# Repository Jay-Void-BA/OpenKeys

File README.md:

# OpenKeys — Classical edition

开源 USB / NFC 认证器，面向个人制作的 **3 把密钥**。当前电路为 **R0.5：本地六位 PIN、十个数字实体键、DFR0555 双行 LCD**；自研运行代码采用 Rust。

> **工程候选，生产放行 BLOCKED。** 已有已布线电路板、制造文件、板级诊断和经过测试的安全模块。完整生产 Root、认证协议与管理通道的实机集成尚未完成，不能将当前诊断固件用于真实账户。

[当前进度](docs/DEVELOPMENT_STATUS.md) · [文档导航](docs/README.md) · [硬件与图纸](hardware/r05/README.md) · [从原材料开始制作](manufacturing/BUILD_R05_ZH.md) · [安全复查](docs/SECURITY_REVIEW_R05.md)

**当前 `main` 为优先开发的经典版，不含 SM2 或后量子算法。** ML-DSA-65 / ML-KEM-768 留在独立的 [PQC 分支](https://github.com/Jay-Void-BA/OpenKeys/tree/pqc)，暂缓实现。两版都优先选择外国芯片，中国芯片作为备选，并核实大陆交付 / 个人三件采购；见[分版规则](docs/EDITIONS.md)。已将安全芯片候选调整为支持传统 RSA 的 SE051C2；见[选型与供电修订](docs/CLASSICAL_SE_POWER_R05.md)。实片 profile / PIN 权限及 RSA 固件仍待集成验证。

*工程图，非实物照片。板体 96 × 112 mm；外壳候选 102 × 118 × 30 mm，待试装。*

## 当前固定需求

| 项目 | 设计目标与现状 |
|---|---|
| 本地身份验证 | 首次开机在钥匙设置六位数字 PIN，十个独立 GPIO 键；没有指纹。改硬件 PIN 清空全部用户数据，第 11 次完整错误猜测触发清空；完整销毁服务尚待集成 |
| 会话授权 | 硬件 PIN 与各协议 PIN 分别缓存，同一已配对认证会话中 30 秒无有效操作锁定；连接 / 保活不续期，断连 / NFC 离场立即锁定，敏感操作仍需实体确认 |
| 显示 | 英文 16 × 2 LCD，DFRobot DFR0555 蓝底白字；现货及版本说明见硬件页 |
| 认证 | FIDO2 / WebAuthn / Passkey、U2F、hmac-secret、凭据管理；OpenPGP / PIV / SSH 为新增待集成目标 |
| OTP 与记录 | TOTP / HOTP 种子不可导出，六位码仅钥匙 LCD 显示；加密 notes / recovery codes；均受本地 PIN 约束 |
| 接口 / 电源 | 唯一外部 USB-C 母口，USB 2.0 数据兼 5 V 充电，另有 NFC；保护型 500 mAh 电池与真实 NTC |
| 管理器 | GPUI 英文桌面原型；macOS / Windows / Linux USB，iOS NFC / USB-C、iPadOS USB-C、Android NFC / USB-C 为交付目标，真实设备后端和移动安装包尚未完成 |

Apple 20 W 充电器使用 **5 V**，不申请 9 V PD。设计输入预算 **0.50 W**，电池侧充电目标上限约 **0.42 W**，实际受负载、温度和限流影响；诊断镜像关闭充电。

## 从这里开始

| 目的 | 入口 |
|---|---|
| 查看电路、PCB、BOM、结构和制造包 | [R0.5 硬件](hardware/r05/README.md) |
| 了解哪些完成、哪些不能交付 | [状态](docs/DEVELOPMENT_STATUS.md)、[安全复查](docs/SECURITY_REVIEW_R05.md) |
| 构建与检查 | [开发起步](docs/GETTING_STARTED.md)、[R05 目标](firmware/r05/README.md)、[GPUI 管理器](apps/manager-gpui/README.md)、[开发包](docs/NATIVE_BUILDS_R05.md) |
| 核查 PIN 缓存与 NFC 边界 | [会话规则](docs/PIN_SESSIONS_R05.md)、[架构](docs/ARCHITECTURE.md) |
| 从原材料、订板到代焊和测试 | [制作手册](manufacturing/BUILD_R05_ZH.md)、[境内渠道](manufacturing/MAINLAND_COMPONENT_CHANNELS.md) |
| 委托个人 / 小批量工厂、实验室 | [机构筛选](manufacturing/MAINLAND_SUPPLIERS_AND_LABS.md)、[资格确认](manufacturing/REQUEST_FOR_CONFIRMATION.md) |
| 比较已拉取的开源实现 | [PicoKeys / OpenSK / CanoKey / SoloKeys 参考](docs/UPSTREAM_REVIEW_R05.md) |

## 检查的含义

R05 当前有 14 页原理图、209 个 BOM 位置、四层已布线 PCB；ERC / DRC 零错误、零警告、零未连接，1187 项独立板网核对通过。[CAD 清单](hardware/r05/review/cad-manifest.json)绑定导出文件。独立备份、主动防拆和隔离采样的[专项测试](manufacturing/BACKUP_TAMPER_TESTS_R05_ZH.md)另行验收；新增五路 NFC 隔离与 VCC 反向阻断须按[NFC 专项规程](manufacturing/NFC_ISOLATION_TESTS_R05_ZH.md)验证。设计文件的规则和连通性不能证明实物抗侧信道、故障注入、EMC、RF、充电或抗拆安全。

新代码的[本地检查记录](docs/r05-validation.json)与 CI 以对应提交为准；[R04 的历史 CI](docs/ci-evidence-r04.json)不能作为 R05 的通过证明。[生产缺口](docs/DEVELOPMENT_STATUS.md)逐项列出，完整 Root 和硬件 PIN 的 SE 原生强制仍是关键未关闭项。

```text
hardware/r05/      当前电路、PCB、BOM、机械和制造导出
firmware/r05/      与 R05 已保存板绑定的 ARM 电气诊断
firmware/board/    LCD、十键、PIN 输入、OTP 等候选驱动
crates/           授权、协议适配、SE、加密通信和存储模块
apps/manager-gpui/ GPUI 管理器原型；设备后端尚未接通
manufacturing/    制作、渠道、委托和验收资料
docs/             状态、安全边界、会话和参考复核
vendor/           固定第三方来源、许可和可核查补丁
```

自研源码采用 [MIT](LICENSE)，硬件采用 [CERN-OHL-S-2.0](hardware/LICENSE-CERN-OHL-S-2.0.txt)；第三方代码保留各自许可。历史 R04 指纹 / 四键资料从[硬件导航](hardware/README.md)进入，不能与 R05 混用。

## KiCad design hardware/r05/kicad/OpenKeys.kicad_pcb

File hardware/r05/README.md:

# OpenKeys R0.5：PIN＋十键

[项目首页](../../README.md) · [状态](../../docs/DEVELOPMENT_STATUS.md) · [安全复查](../../docs/SECURITY_REVIEW_R05.md) · [制作与测试](../../manufacturing/BUILD_R05_ZH.md)

本版正式取消指纹。身份验证使用设备本地 **6 位数字 PIN**，0–9 十个独立实体键；电脑和手机均不输入设备 PIN。保留 FIDO2 / U2F / hmac-secret、可信请求确认、凭据管理和加密 notes / recovery codes 的目标范围。新增 TOTP / HOTP、OpenPGP / PIV / SSH 目标；动态验证码仅钥匙 LCD 显示，种子不可导出。

**工程样板候选，生产放行仍为 BLOCKED。** CAD 检查、Rust 模型测试与诊断固件不能替代生产 Root、实片配置和物理安全验收。不得给三把最终密钥写入真实账户或恢复码。

## 文件

| 内容 | 入口 |
|---|---|
| 整机尺寸与真实 PCB 线条 | [装配图 PDF](exports/OpenKeys-dimensions.pdf)、[PNG](exports/OpenKeys-dimensions.png)、[坐标 JSON](mechanical/dimensions.json) |
| 电路 | [14 页原理图 PDF](exports/OpenKeys-schematic.pdf)、[KiCad 源](kicad/OpenKeys.kicad_sch)、[网表](exports/OpenKeys-netlist.xml) |
| PCB | [四层板源](kicad/OpenKeys.kicad_pcb)、[正面](exports/OpenKeys-PCB-front.svg)、[背面](exports/OpenKeys-PCB-back.svg) |
| 工程打样资料 | [Gerber / 钻孔](exports/OpenKeys-fabrication.zip)、[BOM](BOM.csv)、[贴片坐标](exports/OpenKeys-SMD-position.csv)、[引脚表](pinout.csv) |
| 结构 | [OpenSCAD](mechanical/enclosure.scad)、[板体 STEP](exports/OpenKeys-PCB.step)、[结构导出](exports) |
| 检查 | [ERC](review/erc.json)、[DRC](review/routed-drc.json)、[独立网表核对](review/netlist-check.json)、[板网核对](review/board-check.json)、[摘要](review/cad-manifest.json) |
| 模拟范围 | [天线 / 复位 RC](review/simulation.json)、[输入保护直流角落](review/protection-calculations.json)、[LCD 电压静态角落](review/lcd-voltage-window.json)、[LCD 断电假设模型](review/display-power-model.json)、[备份 / 主动防拆 / ADC 模型](review/backup-tamper-model.json) |

硬件 PIN 与协议 PIN 分别按[同一认证会话的 30 秒规则](../../docs/PIN_SESSIONS_R05.md)缓存；断连 / NFC 离场立即锁定。改硬件 PIN 或第 11 次完整错误须清空全部数据；当前仅擦除锁存，完整销毁服务待集成。

## 经典版 SE 与辅助电源

U5 为 SE051C2HQ1/Z01XDZ / OEF A8FA / Applet 7.2 候选，保留 H573 单 SE 架构，纠正原 E2 不支持 RSA 的限制。VBAT 改用独立预焊脚 CR-2032/HFN，经 10k 限流和 LM66100 反向阻断；CE 必须接 VOUT，不能接地。C41 / C56 在 MCU VBAT 就近去耦。PA1 的硬件 TAMP_OUT4 经三个分散的内部壳体触点返回 PC13 / TAMP_IN1；另一触点 SW12 独立复位。U27 / U24 / U25 / U26 对主动回路失配进行整形、比较、滤波和硬件复位，没有软件使能旁路。备份 SRAM 关闭，连续性锚点使用备份寄存器；Root 连续性集成与实片验证仍是交付条件。

电量采样的 330k / 330k 分压器与储能电容在 TMUX1511 的隔离侧，ADC 侧有 100k 下拉；硬复位切断采样通路。计入下拉负载，正常采样比例为 **100/530**，仍不能把电量电压当成已校准百分比。[电源依据与采购](../../docs/CLASSICAL_SE_POWER_R05.md)、[备份防拆与采样测试](../../manufacturing/BACKUP_TAMPER_TESTS_R05_ZH.md)。

NFC 另增加五路 TMUX1511 信号隔离和 LM66100 VCC 反向阻断，主轨 R69 改 9.1k 泄放；总数 **209 个 BOM 位置**。全部信号隔离的使能硬接 NRST，RF 侧与主机侧不共用铜线。20µA 反灌分配和 <=2MHz 初始 SPI 限制尚待实测，不能外推 ±2µA 的零供电指标到任意电源爬升或强场；见[电路依据](../../docs/CLASSICAL_NFC_ISOLATION_R05.md)、[实板规程](../../manufacturing/NFC_ISOLATION_TESTS_R05_ZH.md)。原生 PIN / RSA、生产 Root 和全数据销毁仍需实际集成；LCD 修订见[电路依据与实测条件](../../docs/CLASSICAL_LCD_POWER_R05.md)。

## LCD 采购与兼容性

选用 **DFRobot DFR0555**：16×2 字符 LCD、蓝底白字、可调背光、I2C、标称 3.3–5V、模块外形 87×32×13mm。2026-11-10 中国大陆[官方商城](https://www.dfrobot.com.cn/goods-1697.html)页面标价 **¥55，显示“有货”**。这是页面核验，未预订三件，也不能保证下单时的库存或发货时间。先确认版本、境内发货和同批数量，再买一个尺寸样品。

[官方文档](https://wiki.dfrobot.com/dfr0555/docs/24390)区分 V1.0 与 V1.1：字符地址均为七位 `0x3E`，背光分别为 `0x60`、`0x6B`。BOM 固定 V1.1；若收到 V1.0，必须改用明确标注的 V1.0 诊断镜像并重新冻结配置，禁止自动探测降级。Rust 驱动见 [dfr0555.rs](../../firmware/board/src/dfr0555.rs)，参考寄存器来源见[来源记录](../../docs/DFR0555_SOURCE.md)。

模块无外部复位脚，因此使用锁存切电和 TCA9517A 双线隔离。U17 TPS3808 的 CT 通过 100k 接 VDD，复位释放后保持清除 180–420ms；必须在其后有新的 PC4 上升沿才能恢复供电。330Ω / 0.25W / 1206 泄放、未上电 ON 下拉和 500ms 软件关断保持用于限制残留。模型依赖“总电容≤100µF、关断注入≤20µA、关断延迟≤5ms”等**待测条件**。背光熄灭本身不等于文字消失。

LCD 改从 **SYS 经负载开关**供电，主电源强制 PWM；独立 U22 监测 SYS 窗口。计入参考 / 电阻 / 输入偏置误差，且假设开关加线束压降≤50mV，静态 LCD 范围为约 **3.3746–4.8596V**。U21 两侧分别为主 3.3V 和 LCD 电源，U23 将 EN 转为对应电平。实测纹波、背供电、功耗、低电量和故障瞬态仍是交付条件；不能把 LCD 高侧接到 MCU / SE 总线。

## 布局与按键

主板本体 96×112×1.0mm，USB 小舌部伸出 2.5mm，总包络 96×114.5mm。外壳候选 102×118×30mm。较大的现货 LCD 需要更大外壳，R0.4 的外壳不兼容。

| 场景 | 实体按键功能 |
|---|---|
| 请求到达，尚未授权 | 5 开始本地 PIN；0 取消。仅接收主机请求不扣 PIN 次数 |
| 输入 PIN | 短按 0–9 输入；长按 9 删除一位；长按 0 取消；只显示星号，满 6 位提交 |
| 验证后审阅请求 | 2 上一页，8 下一页，5 确认，0 取消；完整身份各页写入成功后才能确认 |
| 换场景 / 故障 | 丢弃按住的键，要求全部释放；复位、时钟回退、超时、断连撤销授权 |

采用专用 GPIO，没有键盘矩阵和二极管鬼键问题。25ms 去抖，800ms 长按，只在稳定释放时产生一次事件；组合键、滚键、过长按住和轮询间断不产生确认。[实际 MCU 引脚](pinout.csv)与[目标固件构建约束](../../firmware/r05/build.rs)共同核对，禁止向 R0.4 板烧录 R0.5 镜像。

## 电源、NFC 与制造边界

只有一个外部 USB-C 母口，USB 2.0 数据兼 5V 充电；没有 USB-A。可用合规 USB-C 线接 Apple 20W 充电器，不申请 PD 的 9V 档。设计输入 100mA、约 **0.50W**；电池充电目标 100mA、最高约 **0.42W**，还会受系统负载和输入限流影响。当前诊断镜像保持充电禁止，并非可充电成品固件。

保护型 1S 500mAh 电池须有真实贴附的 10k NTC，先测连接器极性。NFC 沿板左侧布置，不在绕组背后放电池、金属或地平面；LCD 和 PIN 操作需要电池供电且主开关开启，未设计成纯 NFC 取电。旋转后的线圈仍须在实际外壳、电池、手持状态下重新调谐和做手机测试。

J7 是内部 LCD 线束，J2/J6 为内部电池 / NTC；J3 为生产 DNP 的内部调试位置，均不应暴露为第二外部接口。原理图的监督器、SE 使能门和壳体触点提供故障处理路径，不能保证任意短脉冲、桥接、激光或探针攻击均被阻断。

## 重建与核对

使用 KiCad 9、Python 3 / pcbnew，附加导出使用 CairoSVG、OpenSCAD、ngspice 47。日常检查运行 `tools/export.sh`，核对**保存的已布线板**；不要默认重建 / 自动布线。`board.py` 无参数会覆盖布局，只有修改硬件并另行评审时使用。自动路由器不是 CI 的组成部分。

电路或模型修改后，先用 `python3 tools/simulate.py` 与 `python3 tools/calculate_backup.py` 明确重跑被动模拟，再导出。后者保存器件 / 语义网表 / 模型源码摘要；`--check` 和 CAD CI 只核对这些绑定，不声称重新执行 SPICE。所有模型中假定的耗流、容量、漏电、延迟和阈值须按实测更新。

许可：[CERN-OHL-S-2.0](../LICENSE-CERN-OHL-S-2.0.txt)。模型和图纸均标为工程候选；尺寸试装、DFM、EMC / ESD、故障注入和侧信道的实物结果仍为 NOT_RUN。

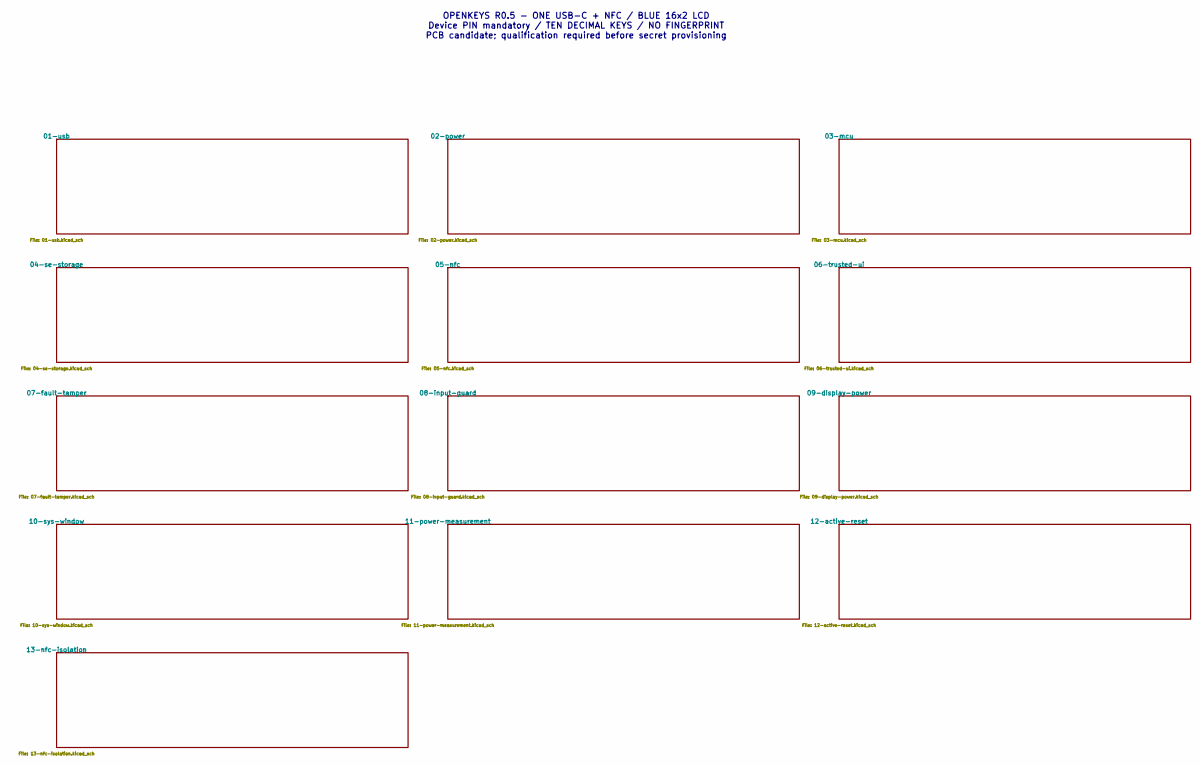
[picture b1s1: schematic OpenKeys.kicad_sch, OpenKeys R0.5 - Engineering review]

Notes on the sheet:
OPENKEYS R0.5 - ONE USB-C + NFC / BLUE 16x2 LCD Device PIN mandatory / TEN DECIMAL KEYS / NO FINGERPRINT PCB candidate; qualification required before secret provisioning

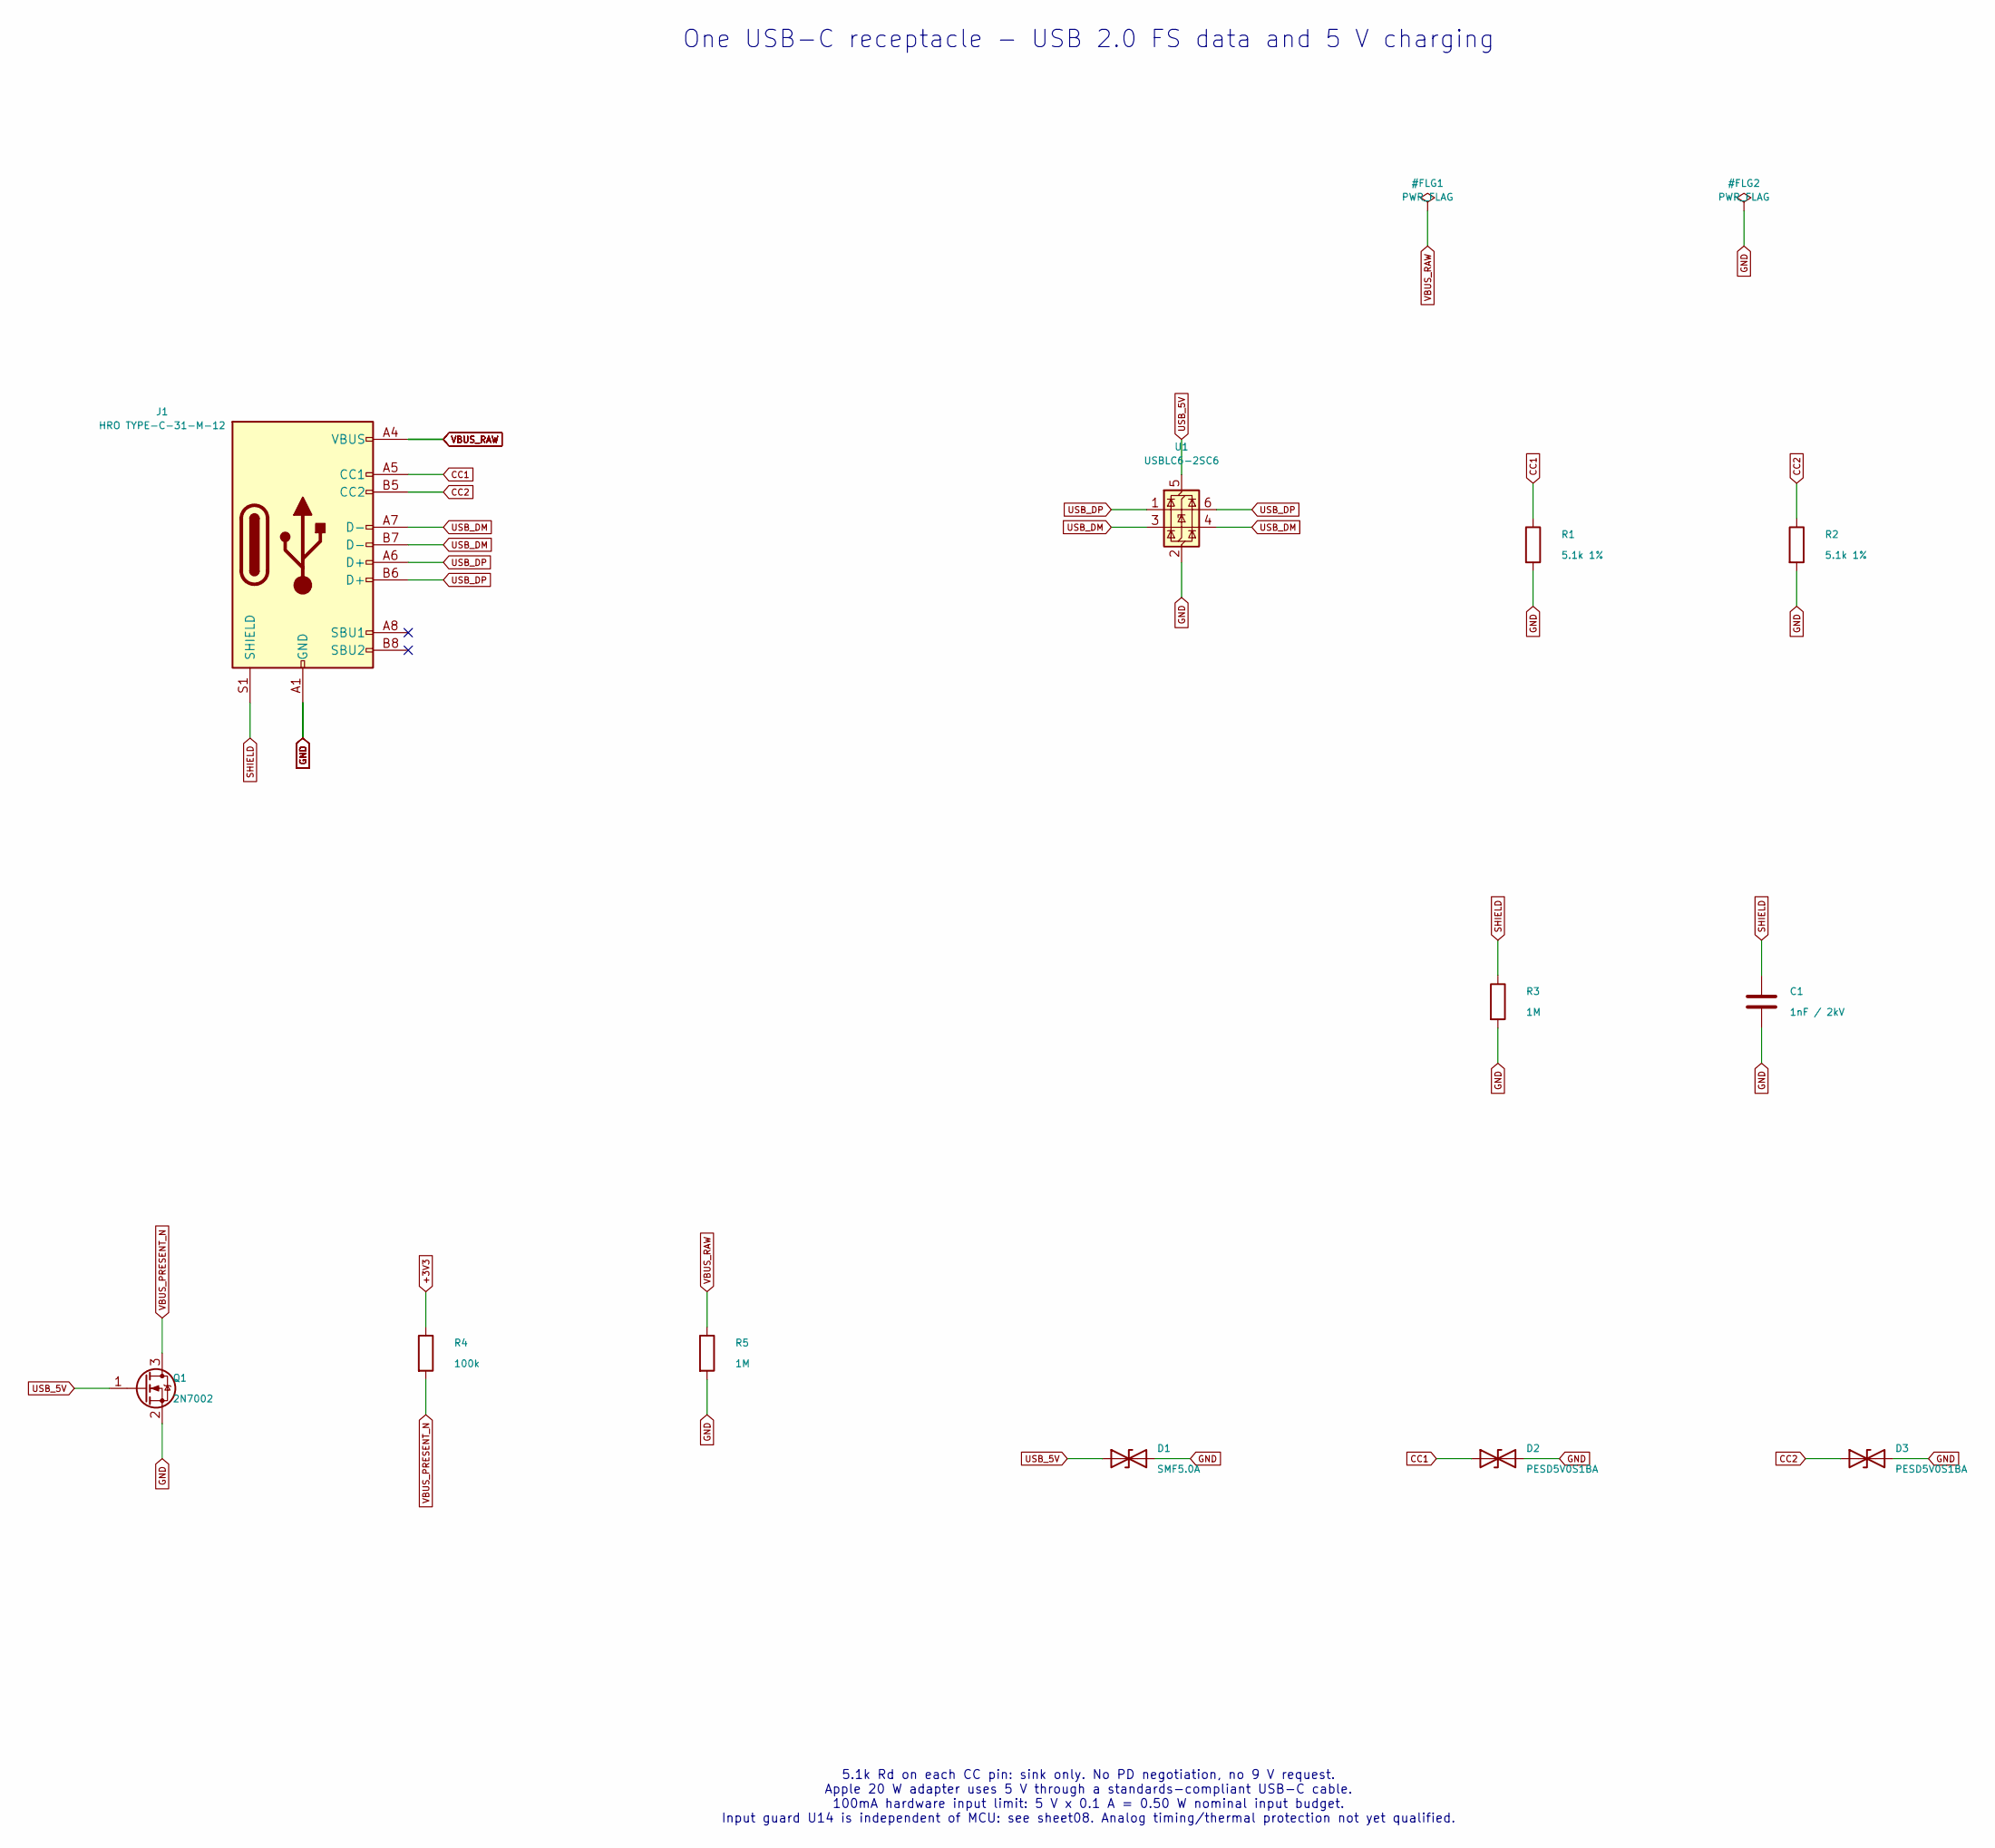
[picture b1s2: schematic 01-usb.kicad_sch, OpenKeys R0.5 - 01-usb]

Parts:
C1: 1nF / 2kV; C_1206_3216Metric
D1: SMF5.0A; D_SOD-123F
D2, D3: PESD5V0S1BA; D_SOD-323
J1: HRO TYPE-C-31-M-12; USB_C_Receptacle_HRO_TYPE-C-31-M-12
Q1: 2N7002; SOT-23
R1, R2: 5.1k 1%; R_0603_1608Metric
R3, R5: 1M; R_0603_1608Metric
R4: 100k; R_0603_1608Metric
U1: USBLC6-2SC6; SOT-23-6

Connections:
+3V3: R4.1; also elsewhere on the board
CC1: D2.1 (A1), J1.A5 (CC1), R1.1
CC2: D3.1 (A1), J1.B5 (CC2), R2.1
GND: C1.2, D1.2 (A2), D2.2 (A2), D3.2 (A2), J1.A1 (GND), J1.A12 (GND), J1.B1 (GND), J1.B12 (GND), Q1.2 (S), R1.2, R2.2, R3.2, R5.2, U1.2 (GND); also elsewhere on the board
SHIELD: C1.1, J1.S1 (SHIELD), R3.1
USB_5V: D1.1 (A1), Q1.1 (G), U1.5 (VBUS); also elsewhere on the board
USB_DM: J1.A7 (D-), J1.B7 (D-), U1.3 (I/O2), U1.4 (I/O2); also elsewhere on the board
USB_DP: J1.A6 (D+), J1.B6 (D+), U1.1 (I/O1), U1.6 (I/O1); also elsewhere on the board
VBUS_PRESENT_N: Q1.3 (D), R4.2; also elsewhere on the board
VBUS_RAW: J1.A4 (VBUS), J1.A9 (VBUS), J1.B4 (VBUS), J1.B9 (VBUS), R5.1; also elsewhere on the board

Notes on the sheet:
One USB-C receptacle - USB 2.0 FS data and 5 V charging
5.1k Rd on each CC pin: sink only. No PD negotiation, no 9 V request. Apple 20 W adapter uses 5 V through a standards-compliant USB-C cable. 100mA hardware input limit: 5 V x 0.1 A = 0.50 W nominal input budget. Input guard U14 is independent of MCU: see sheet08. Analog timing/thermal protection no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

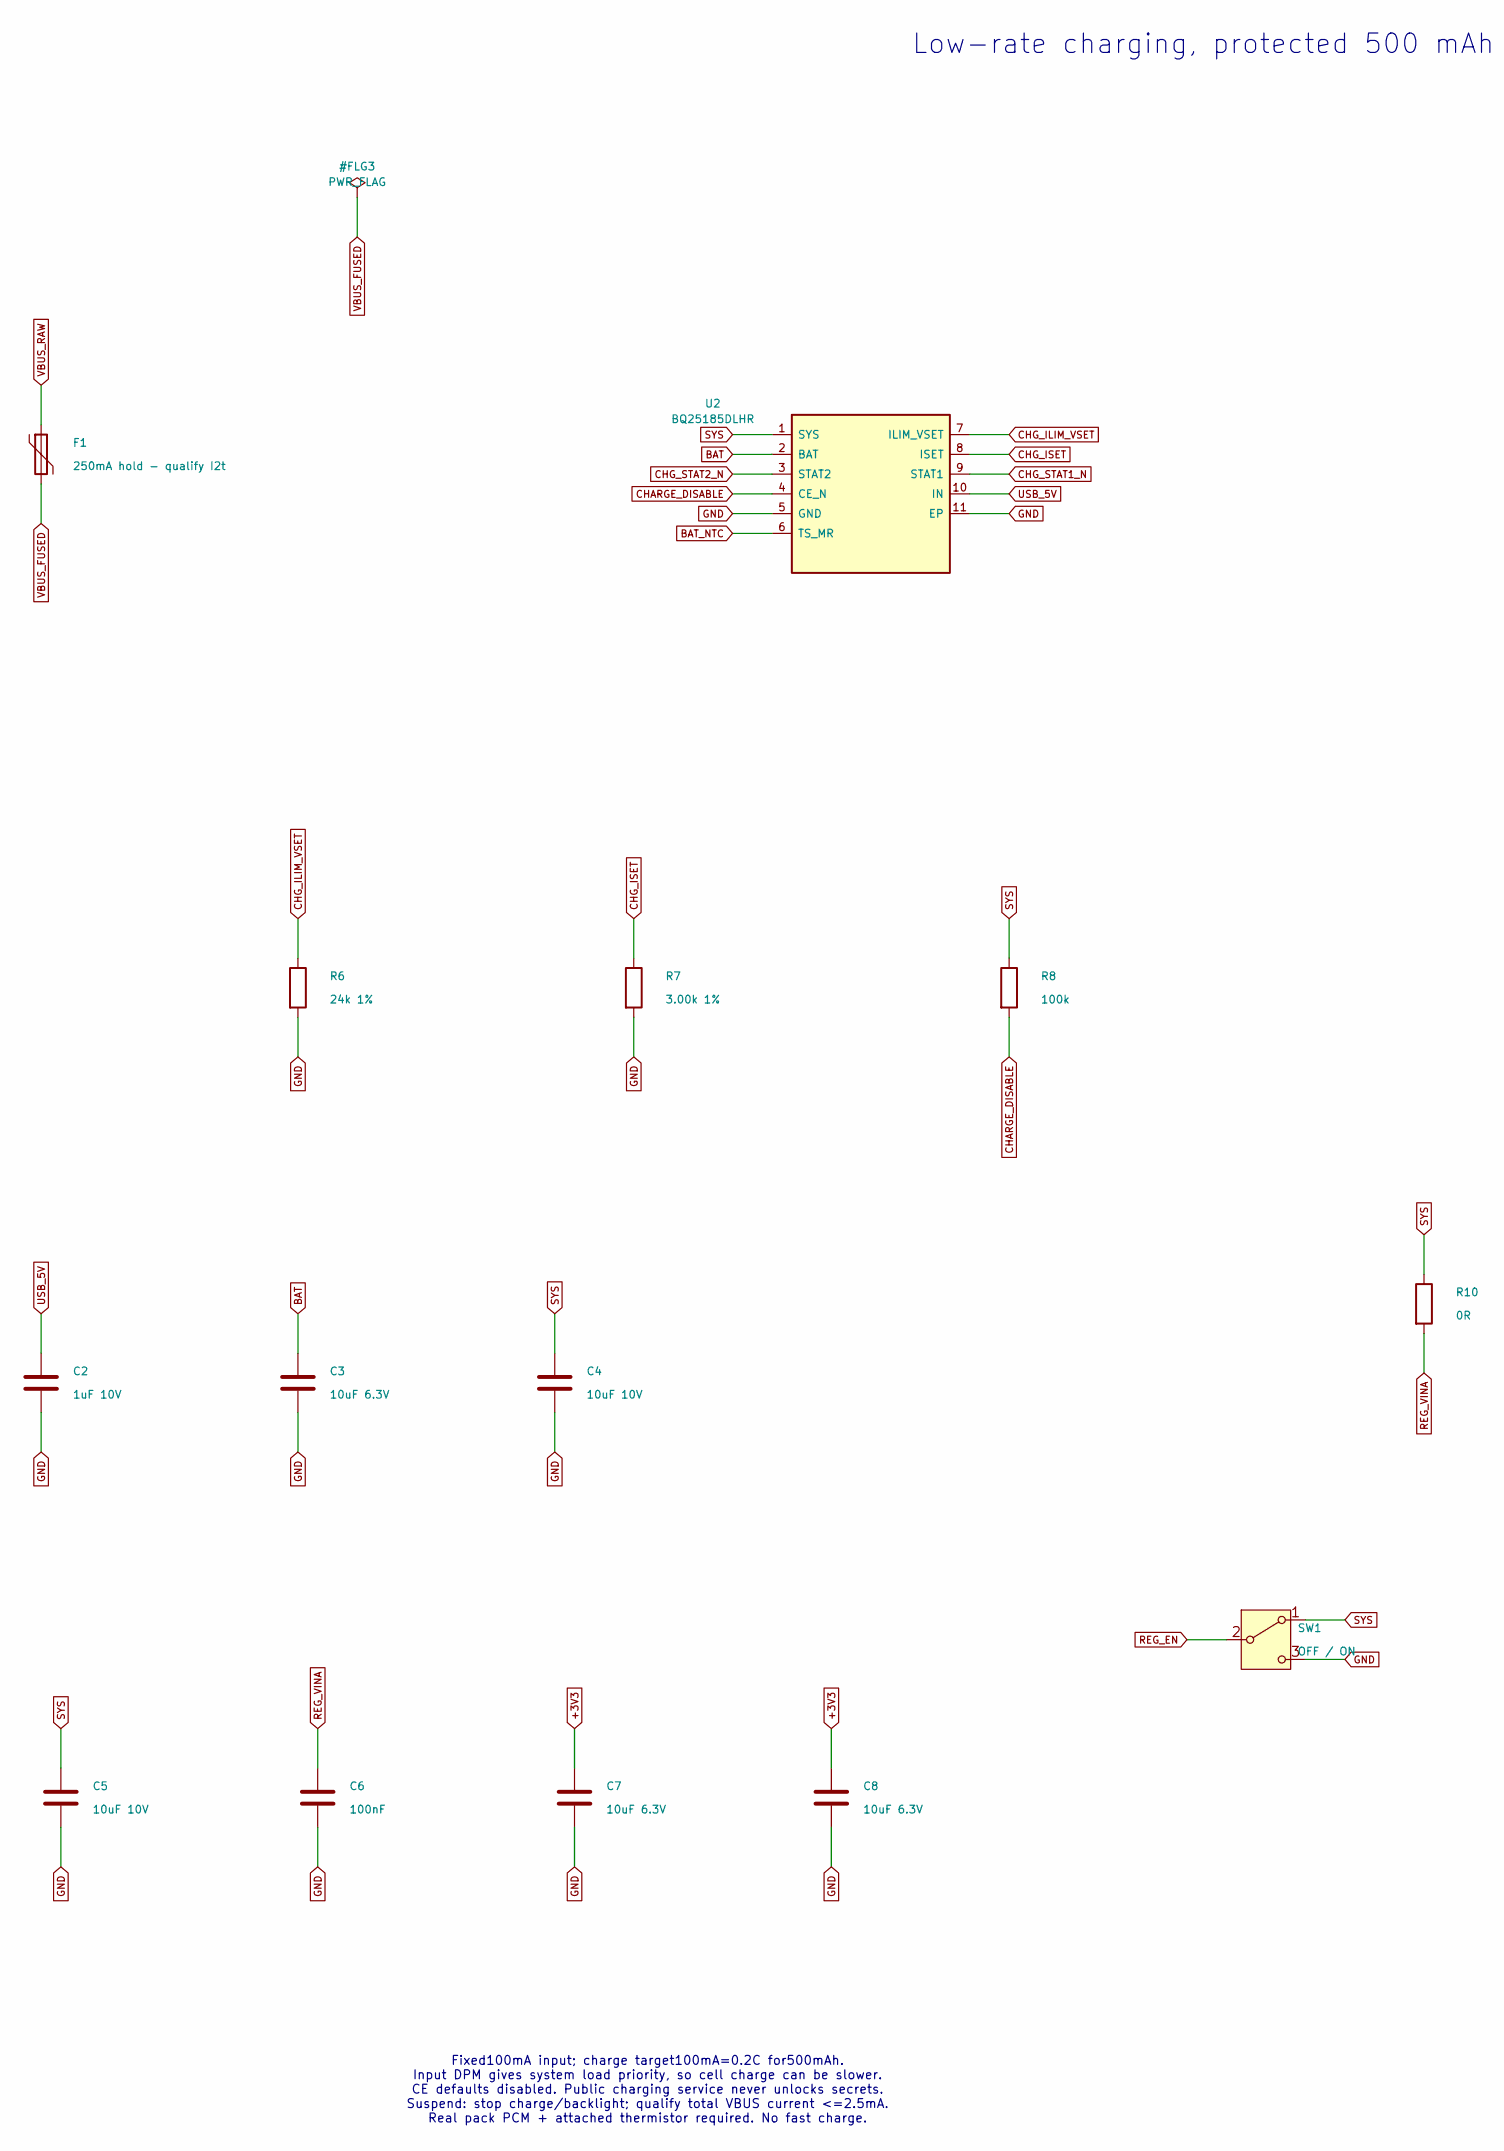
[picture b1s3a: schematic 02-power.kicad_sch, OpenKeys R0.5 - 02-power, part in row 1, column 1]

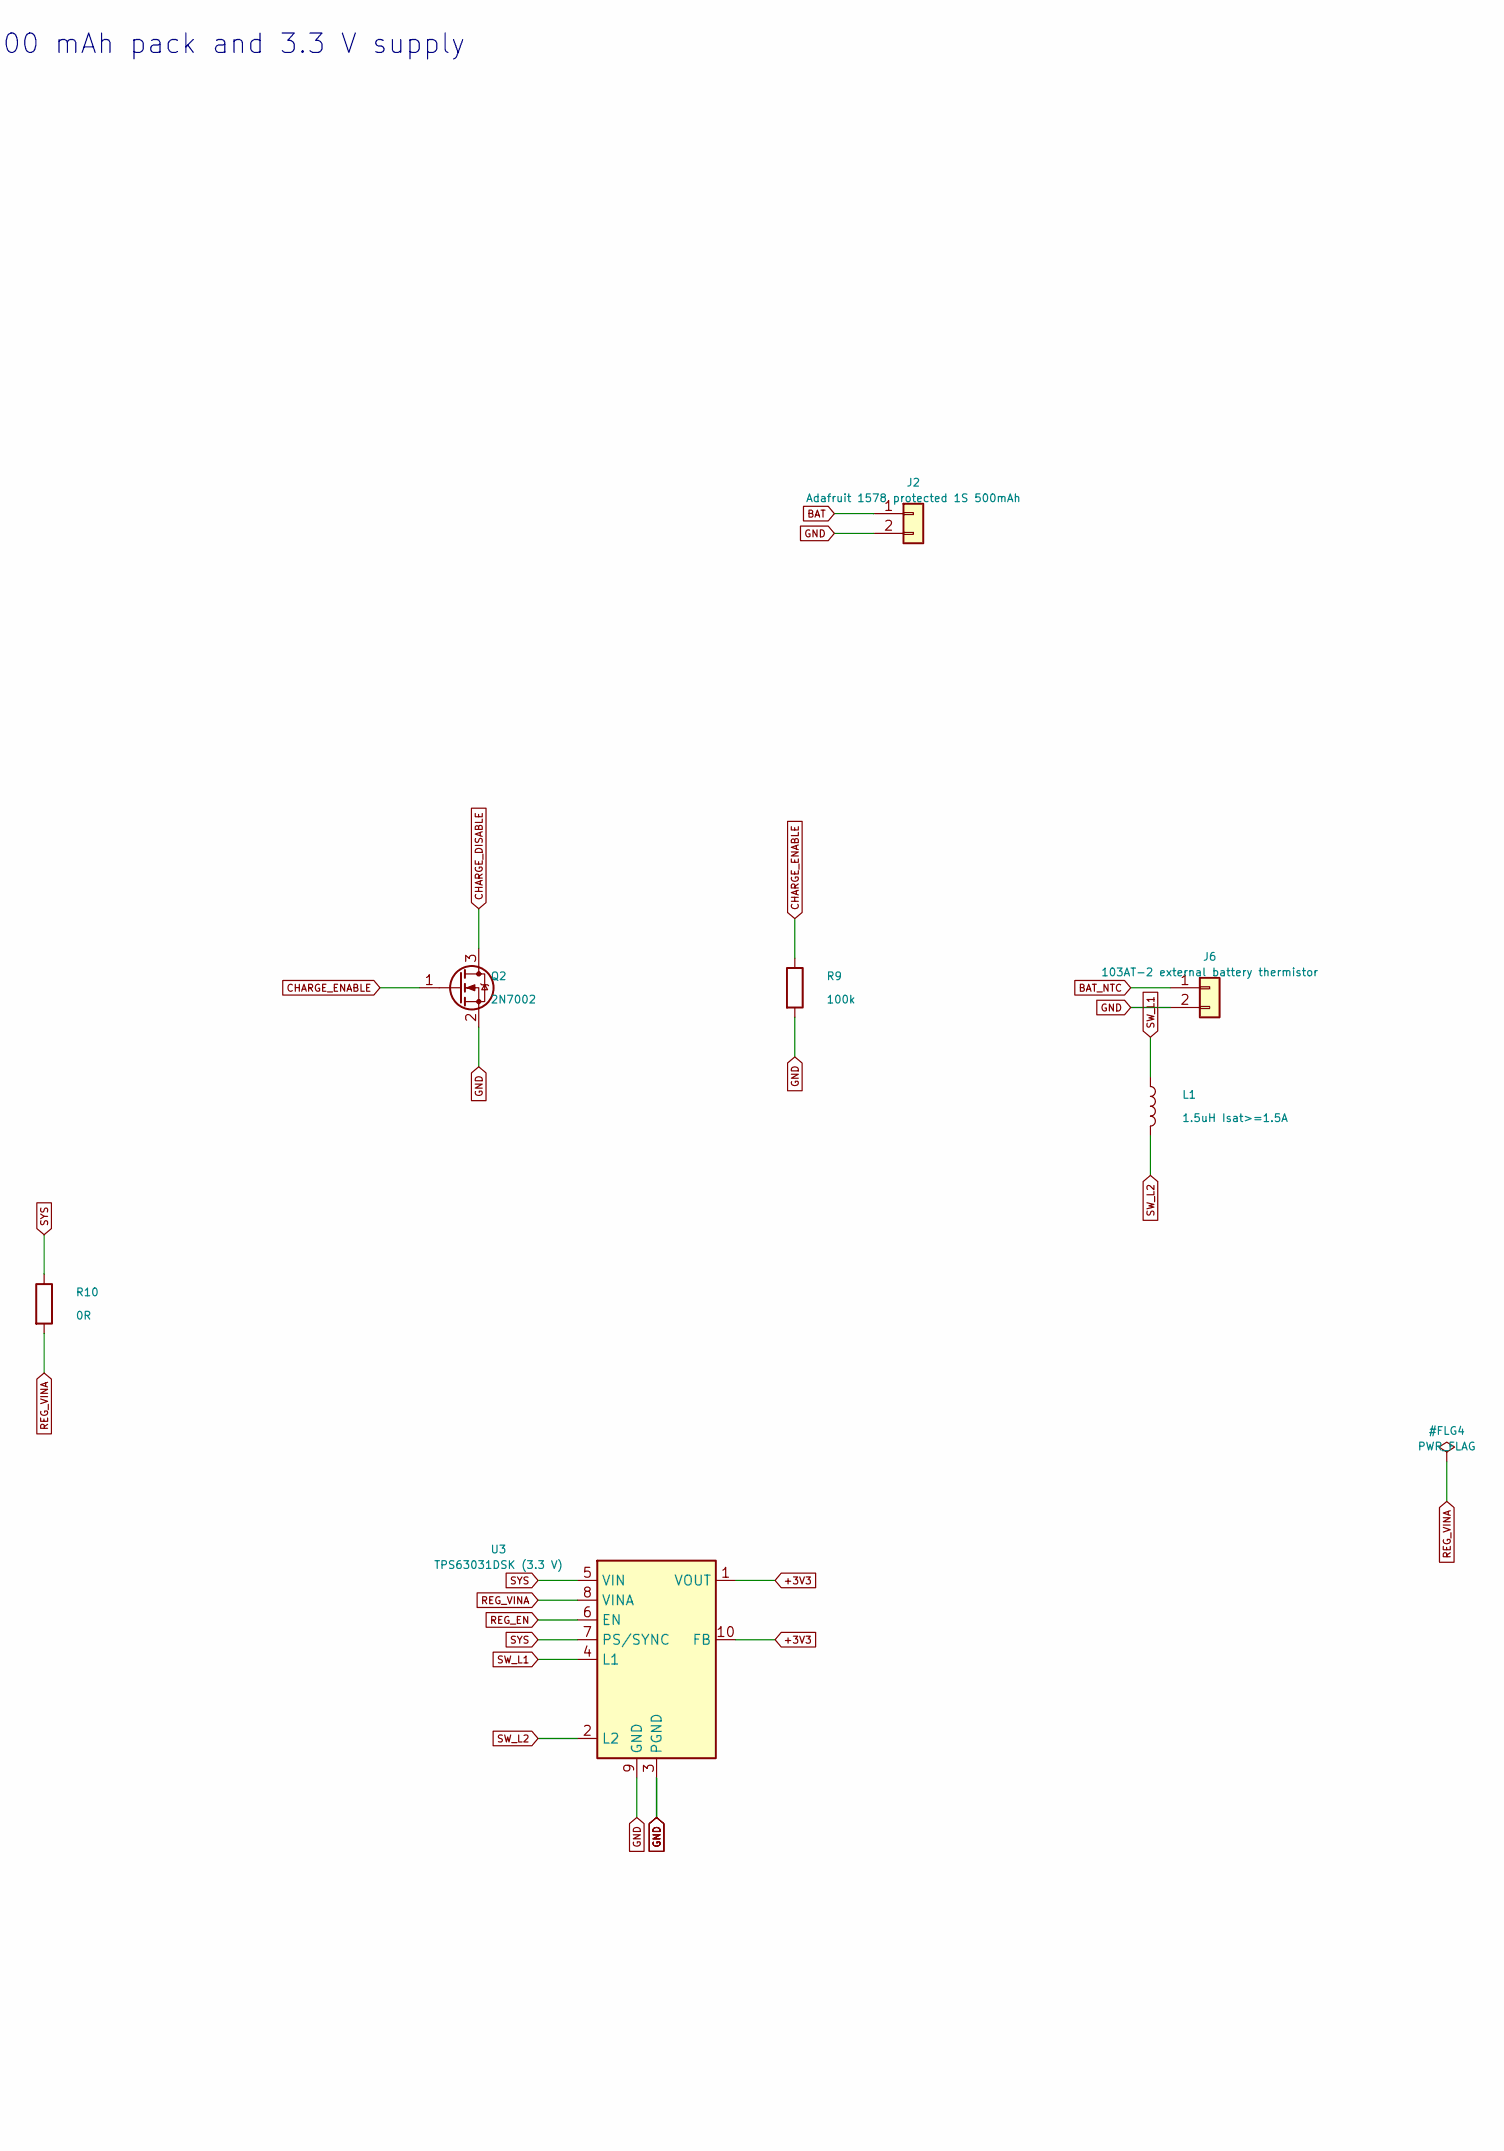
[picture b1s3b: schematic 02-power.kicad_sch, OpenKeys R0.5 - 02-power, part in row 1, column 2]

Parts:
C2: 1uF 10V; C_0805_2012Metric
C3, C7, C8: 10uF 6.3V; C_0805_2012Metric
C4, C5: 10uF 10V; C_0805_2012Metric
C6: 100nF; C_0603_1608Metric
F1: 250mA hold - qualify I2t; Fuse_1206_3216Metric
J2: Adafruit 1578 protected 1S 500mAh; JST_PH_S2B-PH-K_1x02_P2.00mm_Horizontal
J6: 103AT-2 external battery thermistor; JST_SH_SM02B-SRSS-TB_1x02-1MP_P1.00mm_Horizontal
L1: 1.5uH Isat>=1.5A; L_Sunlord_SWPA3015S
Q2: 2N7002; SOT-23
R6: 24k 1%; R_0603_1608Metric
R7: 3.00k 1%; R_0603_1608Metric
R8, R9: 100k; R_0603_1608Metric
R10: 0R; R_0603_1608Metric
SW1: OFF / ON; SW_SPDT_CK_JS102011SAQN
U2: BQ25185DLHR; Texas_DLH0010A_WSON-10-1EP_2.2x2mm_P0.4mm_EP0.9x1.5mm
U3: TPS63031DSK (3.3 V); WSON-10-1EP_2.5x2.5mm_P0.5mm_EP1.2x2mm

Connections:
+3V3: C7.1, C8.1, U3.1 (VOUT), U3.10 (FB); also elsewhere on the board
BAT: C3.1, J2.1, U2.2 (BAT); also elsewhere on the board
BAT_NTC: J6.1, U2.6 (TS_MR)
CHARGE_DISABLE: Q2.3 (D), R8.2, U2.4 (CE_N)
CHARGE_ENABLE: Q2.1 (G), R9.1; also elsewhere on the board
CHG_ILIM_VSET: R6.1, U2.7 (ILIM_VSET)
CHG_ISET: R7.1, U2.8 (ISET)
CHG_STAT1_N: U2.9 (STAT1); also elsewhere on the board
CHG_STAT2_N: U2.3 (STAT2); also elsewhere on the board
GND: C2.2, C3.2, C4.2, C5.2, C6.2, C7.2, C8.2, J2.2, J6.2, Q2.2 (S), R6.2, R7.2, R9.2, SW1.3 (C), U2.5 (GND), U2.11 (EP), U3.3 (PGND), U3.9 (GND), U3.11 (PGND); also elsewhere on the board
REG_EN: SW1.2 (B), U3.6 (EN)
REG_VINA: C6.1, R10.2, U3.8 (VINA)
SW_L1: L1.1, U3.4 (L1)
SW_L2: L1.2, U3.2 (L2)
SYS: C4.1, C5.1, R8.1, R10.1, SW1.1 (A), U2.1 (SYS), U3.5 (VIN), U3.7 (PS/SYNC); also elsewhere on the board
USB_5V: C2.1, U2.10 (IN); also elsewhere on the board
VBUS_FUSED: F1.2; also elsewhere on the board
VBUS_RAW: F1.1; also elsewhere on the board

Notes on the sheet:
Low-rate charging, protected 500 mAh pack and 3.3 V supply
Fixed100mA input; charge target100mA=0.2C for500mAh. Input DPM gives system load priority, so cell charge can be slower. CE defaults disabled. Public charging service never unlocks secrets. Suspend: stop charge/backlight; qualify total VBUS current <=2.5mA. Real pack PCM + attached thermistor requi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

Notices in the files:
hardware/r04/tools/board.py:
SPDX-License-Identifier: CERN-OHL-S-2.0
